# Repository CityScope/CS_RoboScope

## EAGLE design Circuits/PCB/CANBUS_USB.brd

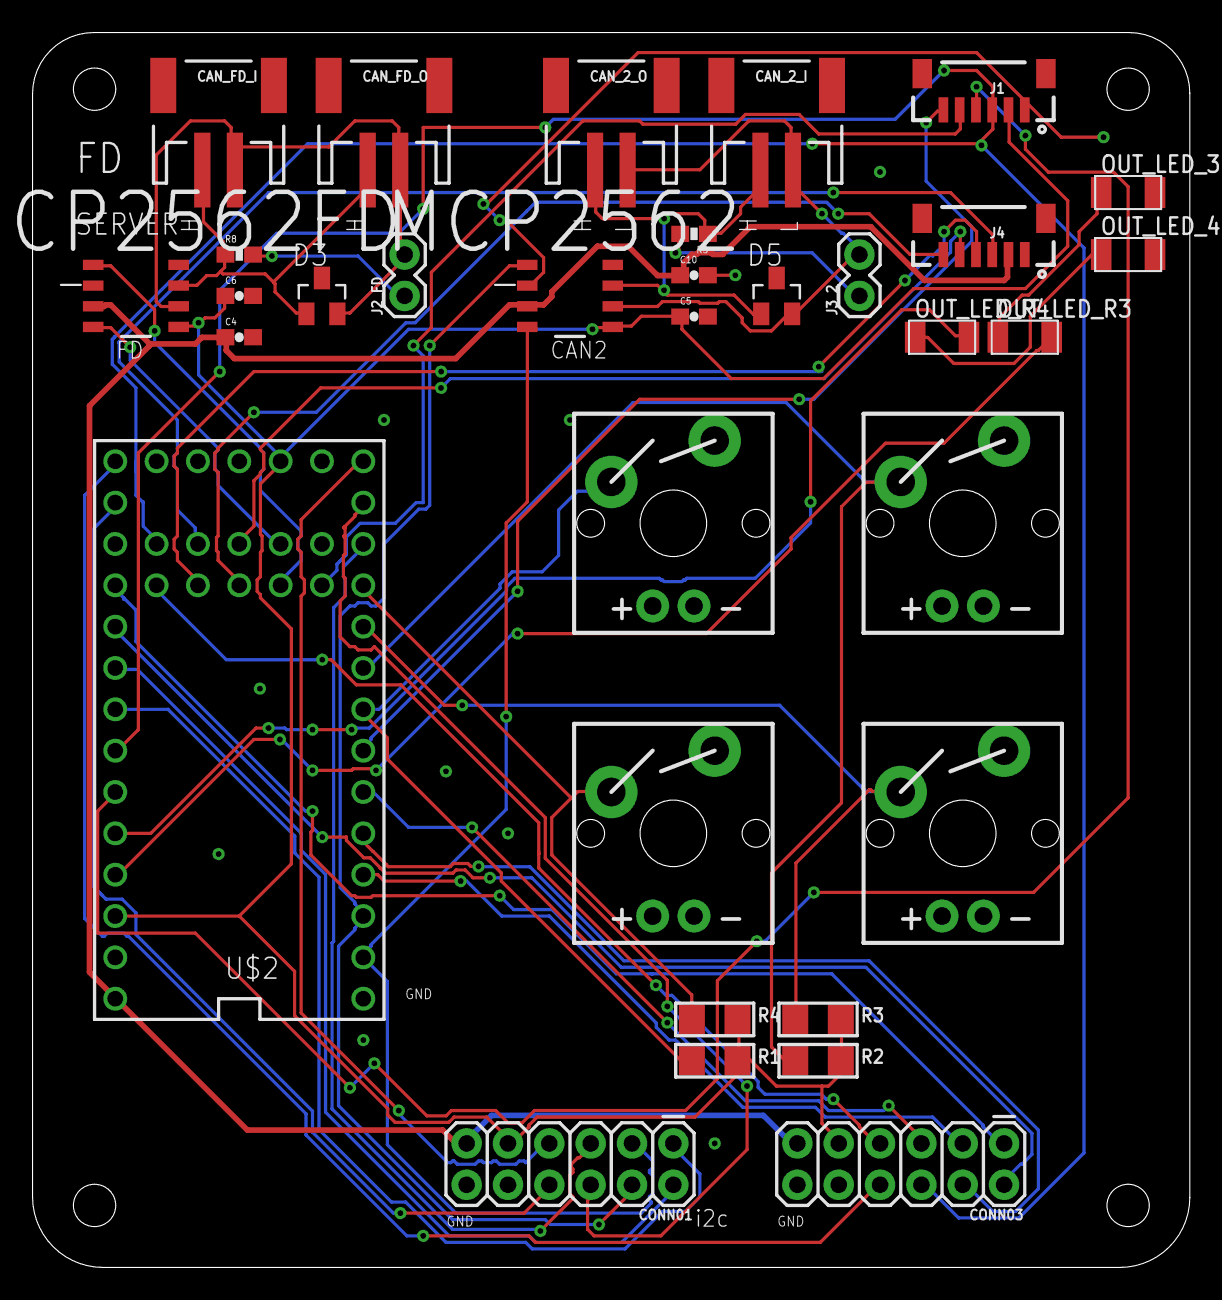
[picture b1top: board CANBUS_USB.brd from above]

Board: 2 copper layers, 71.1 x 75.9 mm, 33 parts (0 on the bottom side), 43 nets.

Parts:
C4, C5, C6, C10: 0.1uf; 0603-CAP
CAN_2_I, CAN_2_O: JST-2-SMD
CAN_FD_I: JST-2-SMD
CAN_FD_O: JST-2-SMD
CONN01, CONN03: 2X6 FEMALE; 2X6
D3, D5: PESD1CAN; SOT23
J1, J4: 1X06-1MM
J2_FD, J3_2: 1X02
MCP2562, MCP2562FD: MCP2562
OUT_LED_3, OUT_LED_4: LEDFAB1206; LED1206FAB
OUT_LED_R3, OUT_LED_R4: 500; R1206FAB
R1, R2, R3, R4: 1206
R5: 120Ohms; 0603-RES
R8: 120Ohms FD; 0603-RES
S1, S2, S3, S4: CHERRY-MX-LED
U$2: TEENSY_4.0_WITH_SMD_HEADER_PINS

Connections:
3.3V: C5.1, C6.1, CONN01.9, CONN03.9, J1.2, MCP2562.VIO, MCP2562FD.VIO, R1.2, R2.2, R3.2, R4.2, U$2.3.3V, U$2.3.3V1
CAN_H: CAN_FD_I.1, CAN_FD_O.1, D3.1, MCP2562FD.CANH, R8.1
CAN_H1: CAN_2_I.1, CAN_2_O.1, D5.1, MCP2562.CANH, R5.1
CAN_L: CAN_FD_I.2, CAN_FD_O.2, D3.2, J2_FD.2, MCP2562FD.CANL
CAN_L1: CAN_2_I.2, CAN_2_O.2, D5.2, J3_2.2, MCP2562.CANL
CAN_RX2: CONN01.3, MCP2562.RXD, U$2.0
CAN_RX3: MCP2562FD.RXD, U$2.30
CAN_TX2: CONN01.4, MCP2562.TXD, U$2.1
CAN_TX3: MCP2562FD.TXD, U$2.31
GND_MCU: C4.2, C5.2, C6.2, C10.2, CONN01.10, CONN01.12, CONN03.10, CONN03.12, D3.3, D5.3, J1.1, J4.1, MCP2562.STBY, MCP2562.VSS, MCP2562FD.STBY, MCP2562FD.VSS, OUT_LED_3.2, OUT_LED_4.2, S1.S2, S2.S2, S3.S2, S4.S2, U$2.GND, U$2.GND1, U$2.GND2
GPIO_01: CONN03.3, U$2.2
GPIO_02: CONN03.4, U$2.3
GPIO_03: CONN03.5, U$2.4
GPIO_04: CONN01.5, U$2.10
GPIO_05: CONN01.6, U$2.11
GPIO_06: CONN01.7, U$2.12
GPIO_07: CONN03.8, U$2.13
GPIO_08: CONN01.8, U$2.14/A0
GPIO_10: CONN03.1, U$2.16/A2
GPIO_11: CONN03.2, U$2.17/A3
GPIO_12: J1.3, U$2.20/A6
GPIO_13: J1.4, U$2.21/A7
GPIO_14: CONN03.7, U$2.25
GPIO_15: J4.3, U$2.26
GPIO_16: J4.4, U$2.27
GPIO_17: J4.5, U$2.28
GPIO_18: J4.6, U$2.29
GPIO_20: CONN03.6, U$2.24
GPIO_SCL: CONN01.1, U$2.19/A5
GPIO_SDA: CONN01.2, U$2.18/A4
KEY_01: R1.1, S1.S1, U$2.6
KEY_02: R2.1, S2.S1, U$2.7
KEY_03: R3.1, S3.S1, U$2.8
KEY_04: R4.1, S4.S1, U$2.9
LED_15: OUT_LED_R4.2, U$2.22/A8
LED_16: OUT_LED_R3.2, U$2.23/A9
unnamed: J2_FD.1, R8.2
unnamed: J3_2.1, R5.2
unnamed: OUT_LED_3.1, OUT_LED_R3.1
unnamed: OUT_LED_4.1, OUT_LED_R4.1
SWITCH_01: J1.6, U$2.5
SWITCH_02: J1.5, U$2.33
VCC_5V: C4.1, C10.1, CONN01.11, CONN03.11, J4.2, MCP2562.VDD, MCP2562FD.VDD, U$2.VIN

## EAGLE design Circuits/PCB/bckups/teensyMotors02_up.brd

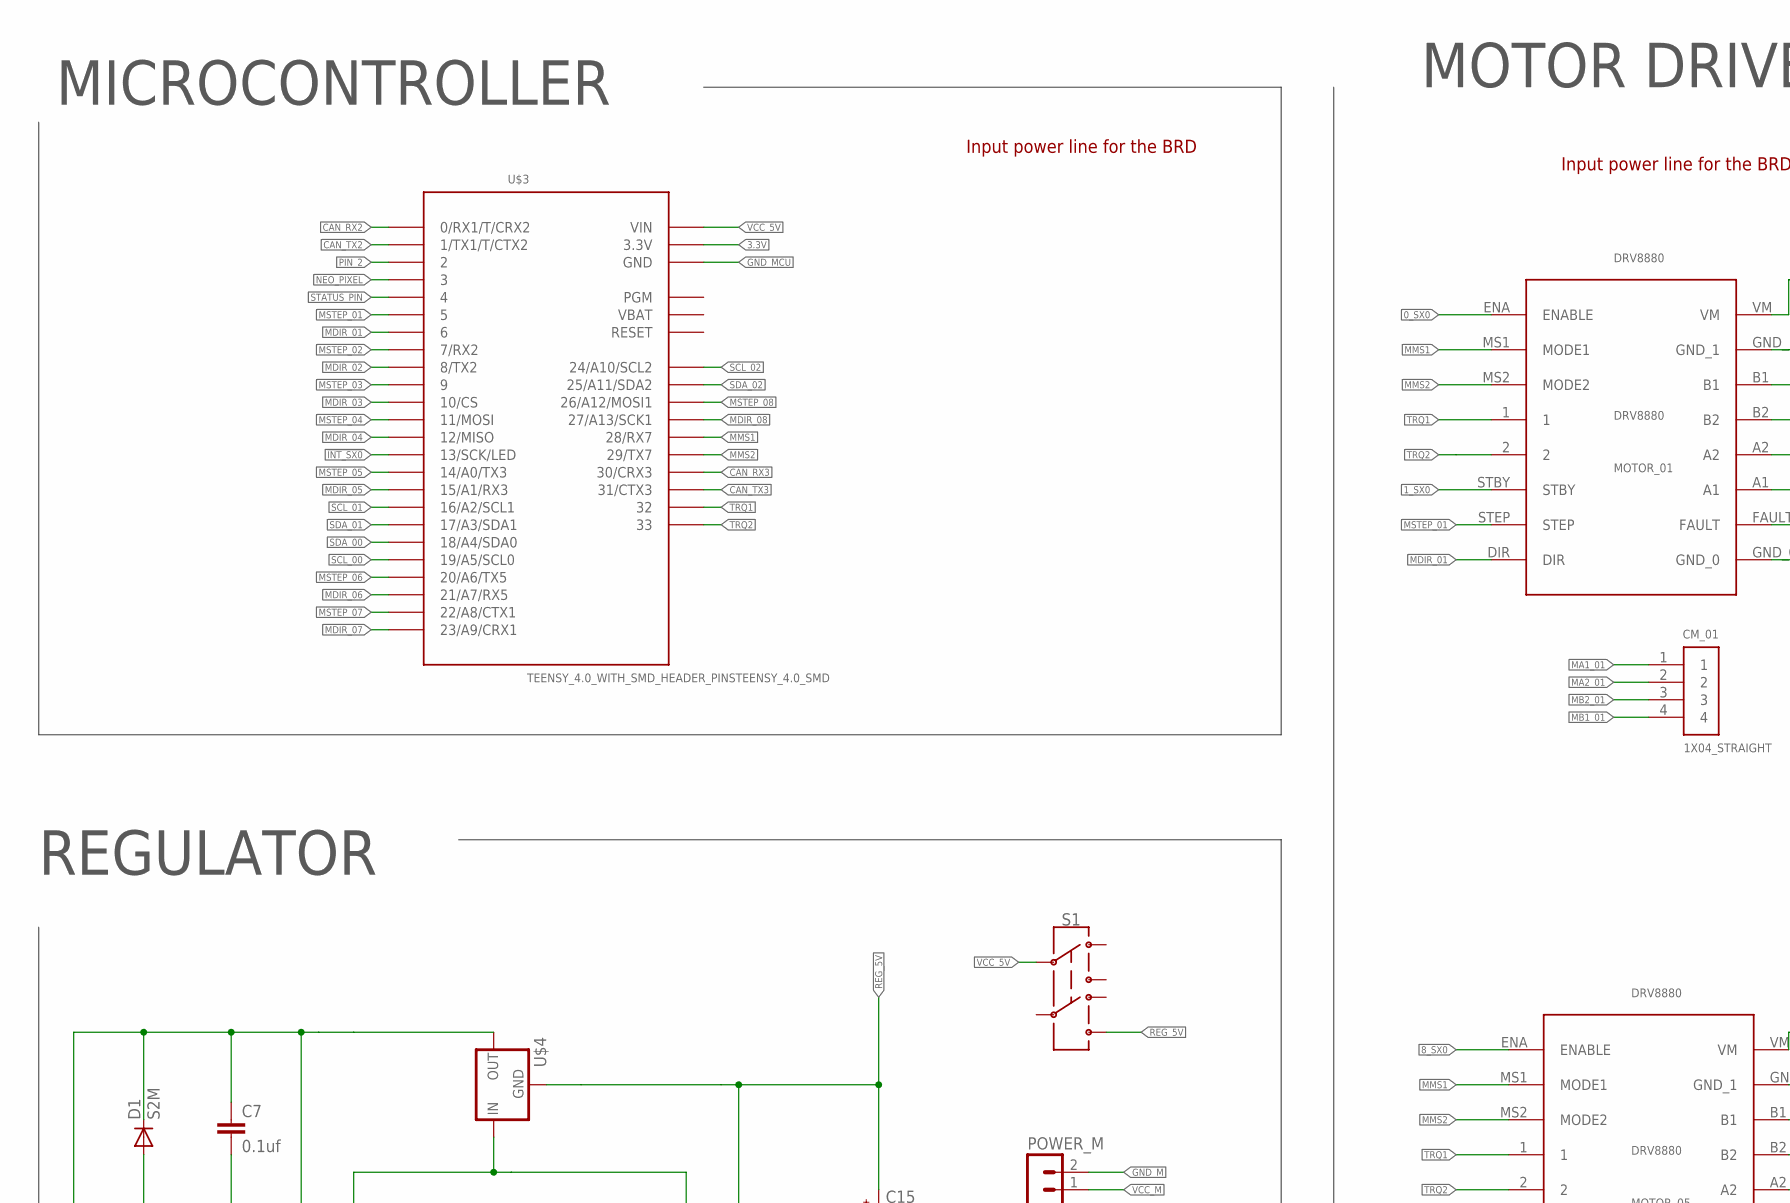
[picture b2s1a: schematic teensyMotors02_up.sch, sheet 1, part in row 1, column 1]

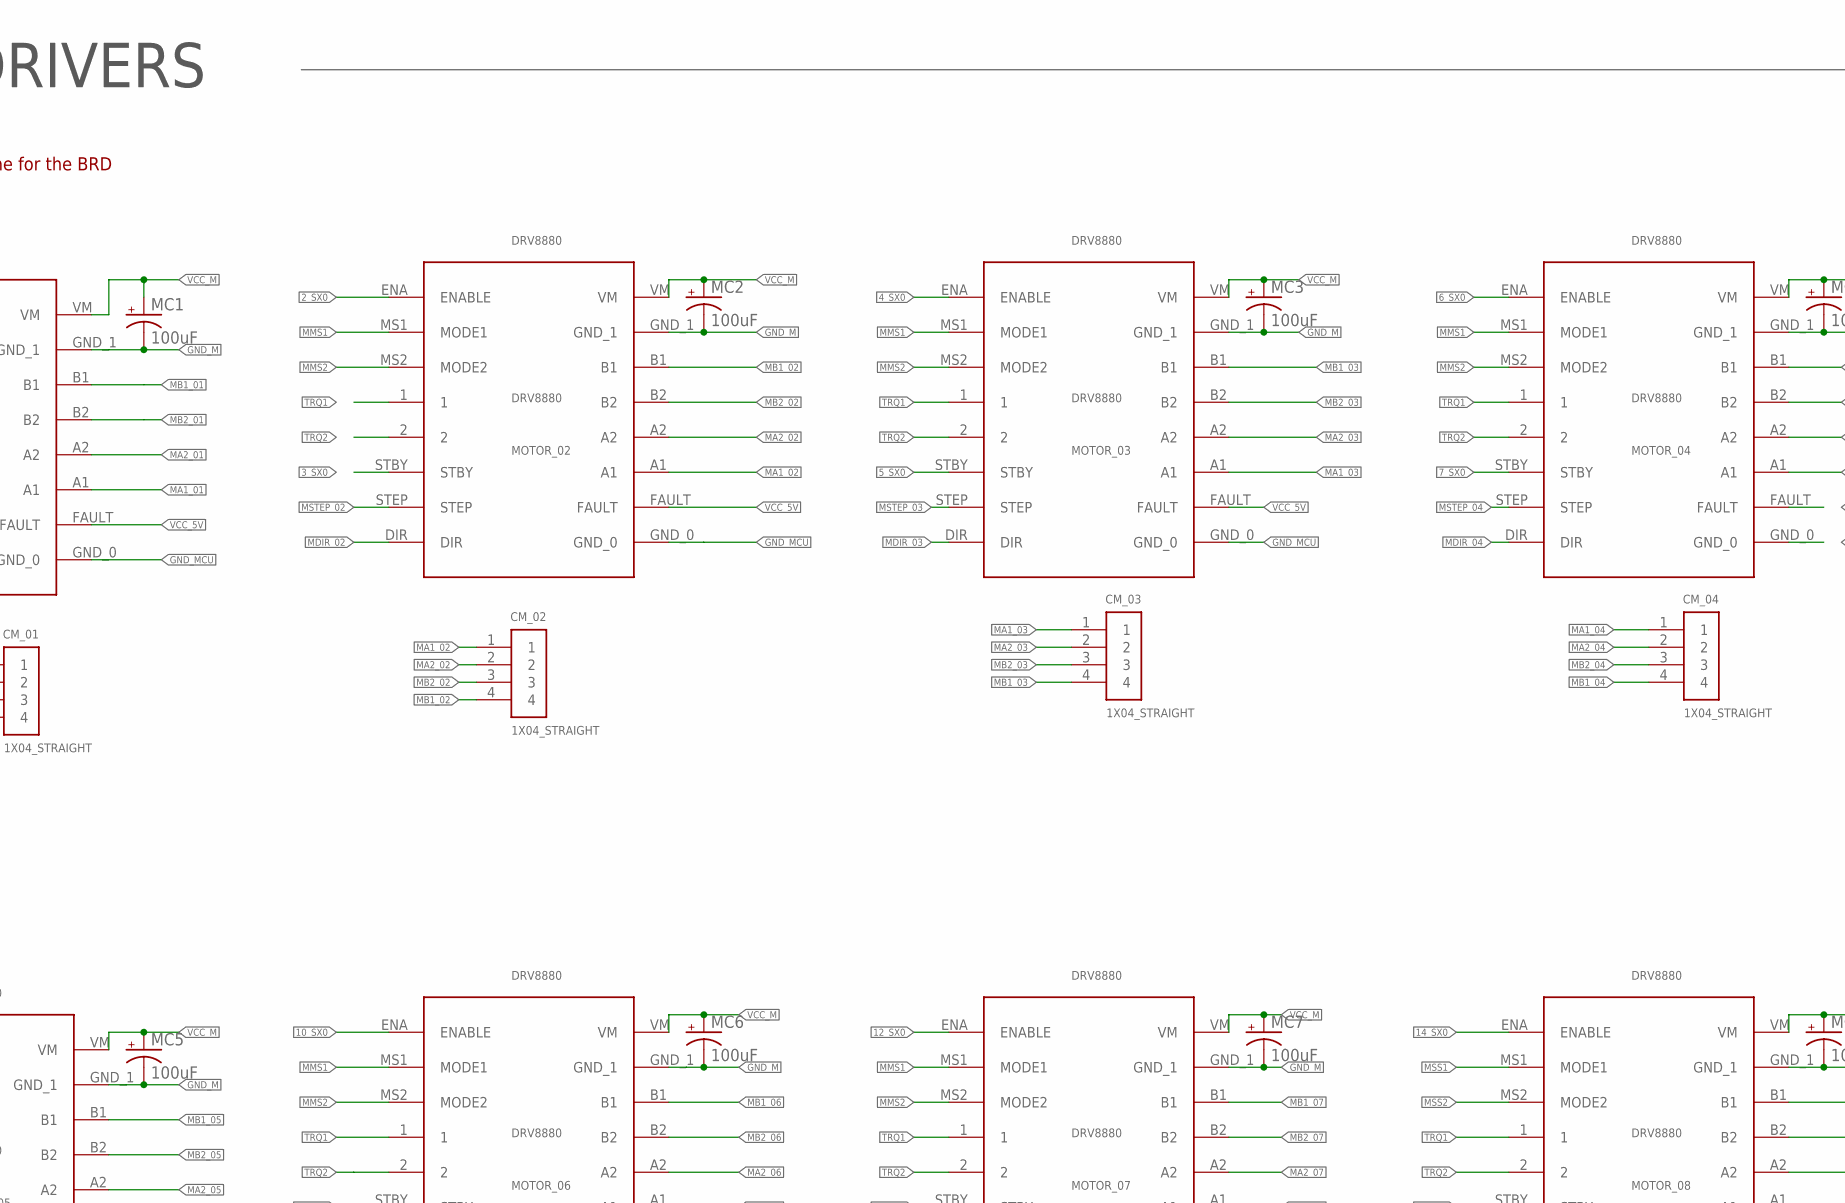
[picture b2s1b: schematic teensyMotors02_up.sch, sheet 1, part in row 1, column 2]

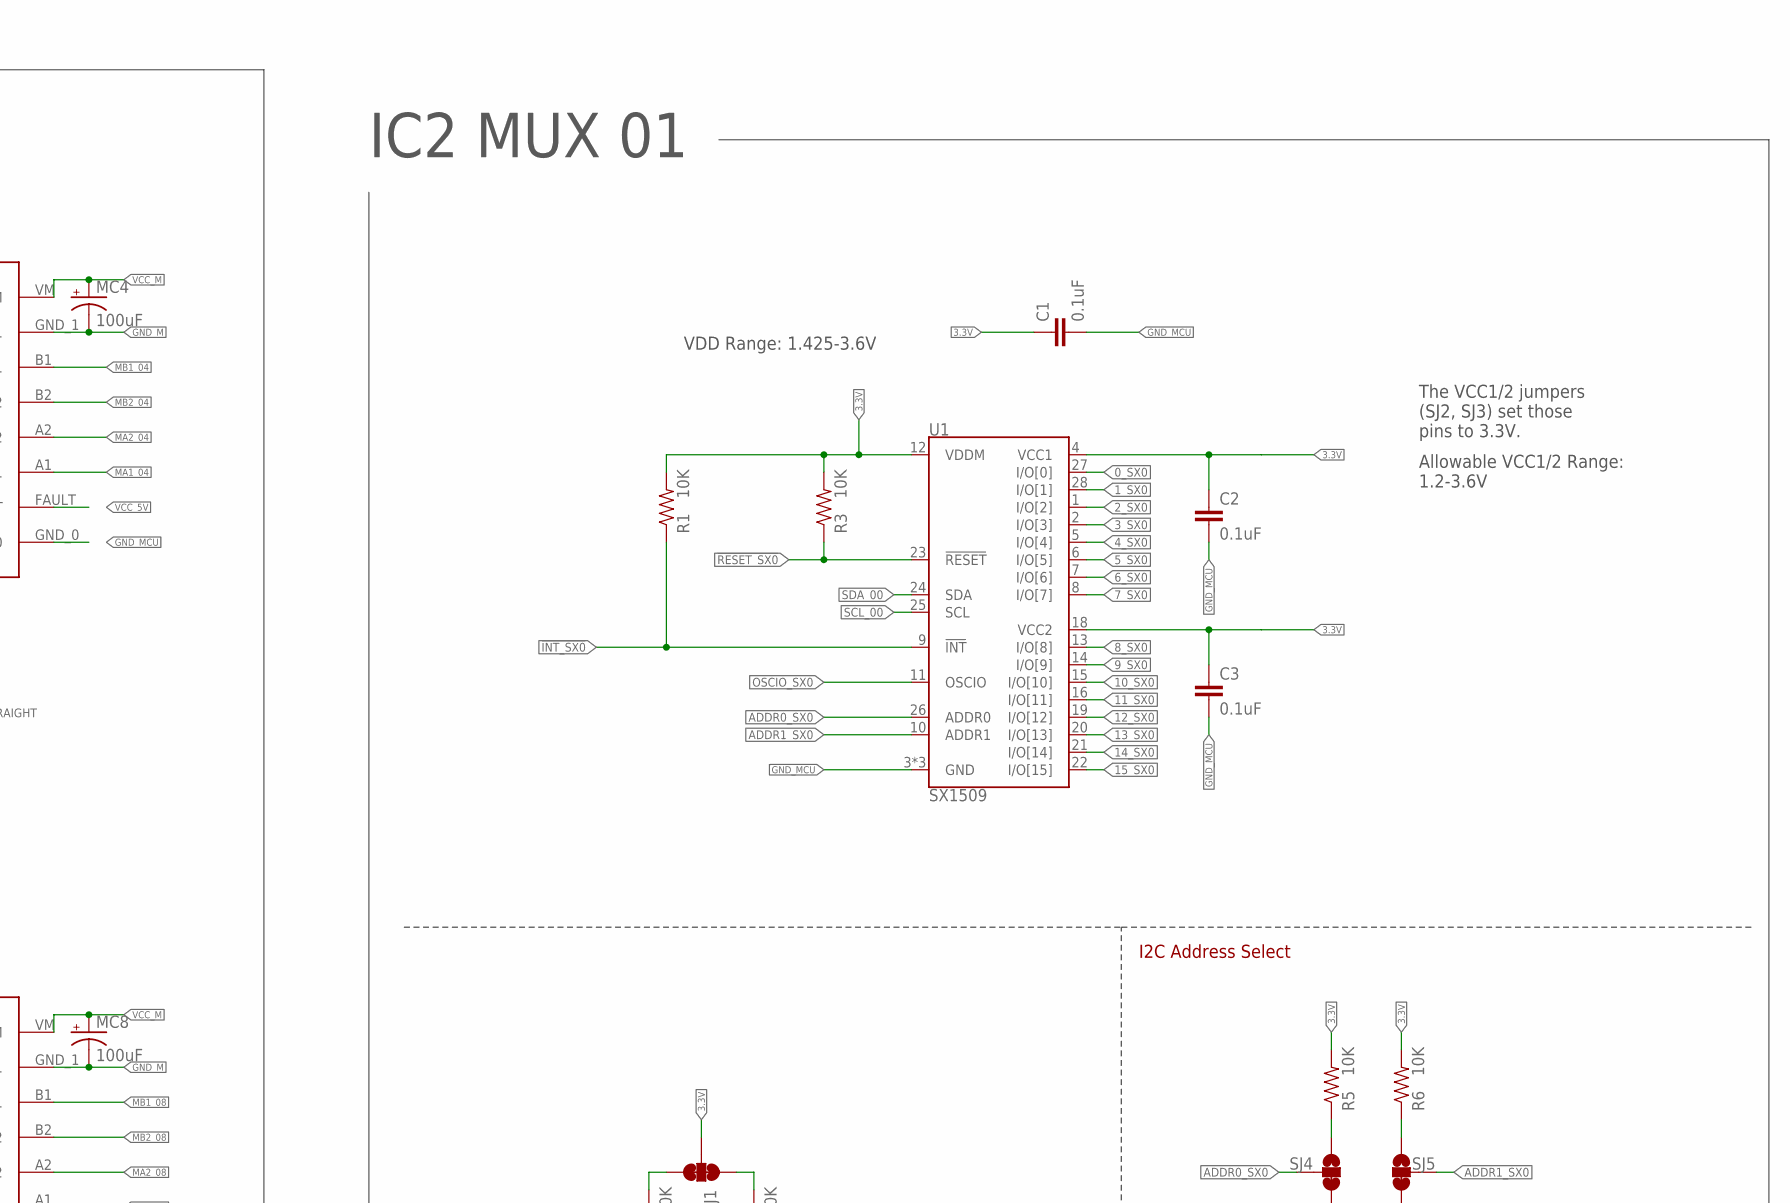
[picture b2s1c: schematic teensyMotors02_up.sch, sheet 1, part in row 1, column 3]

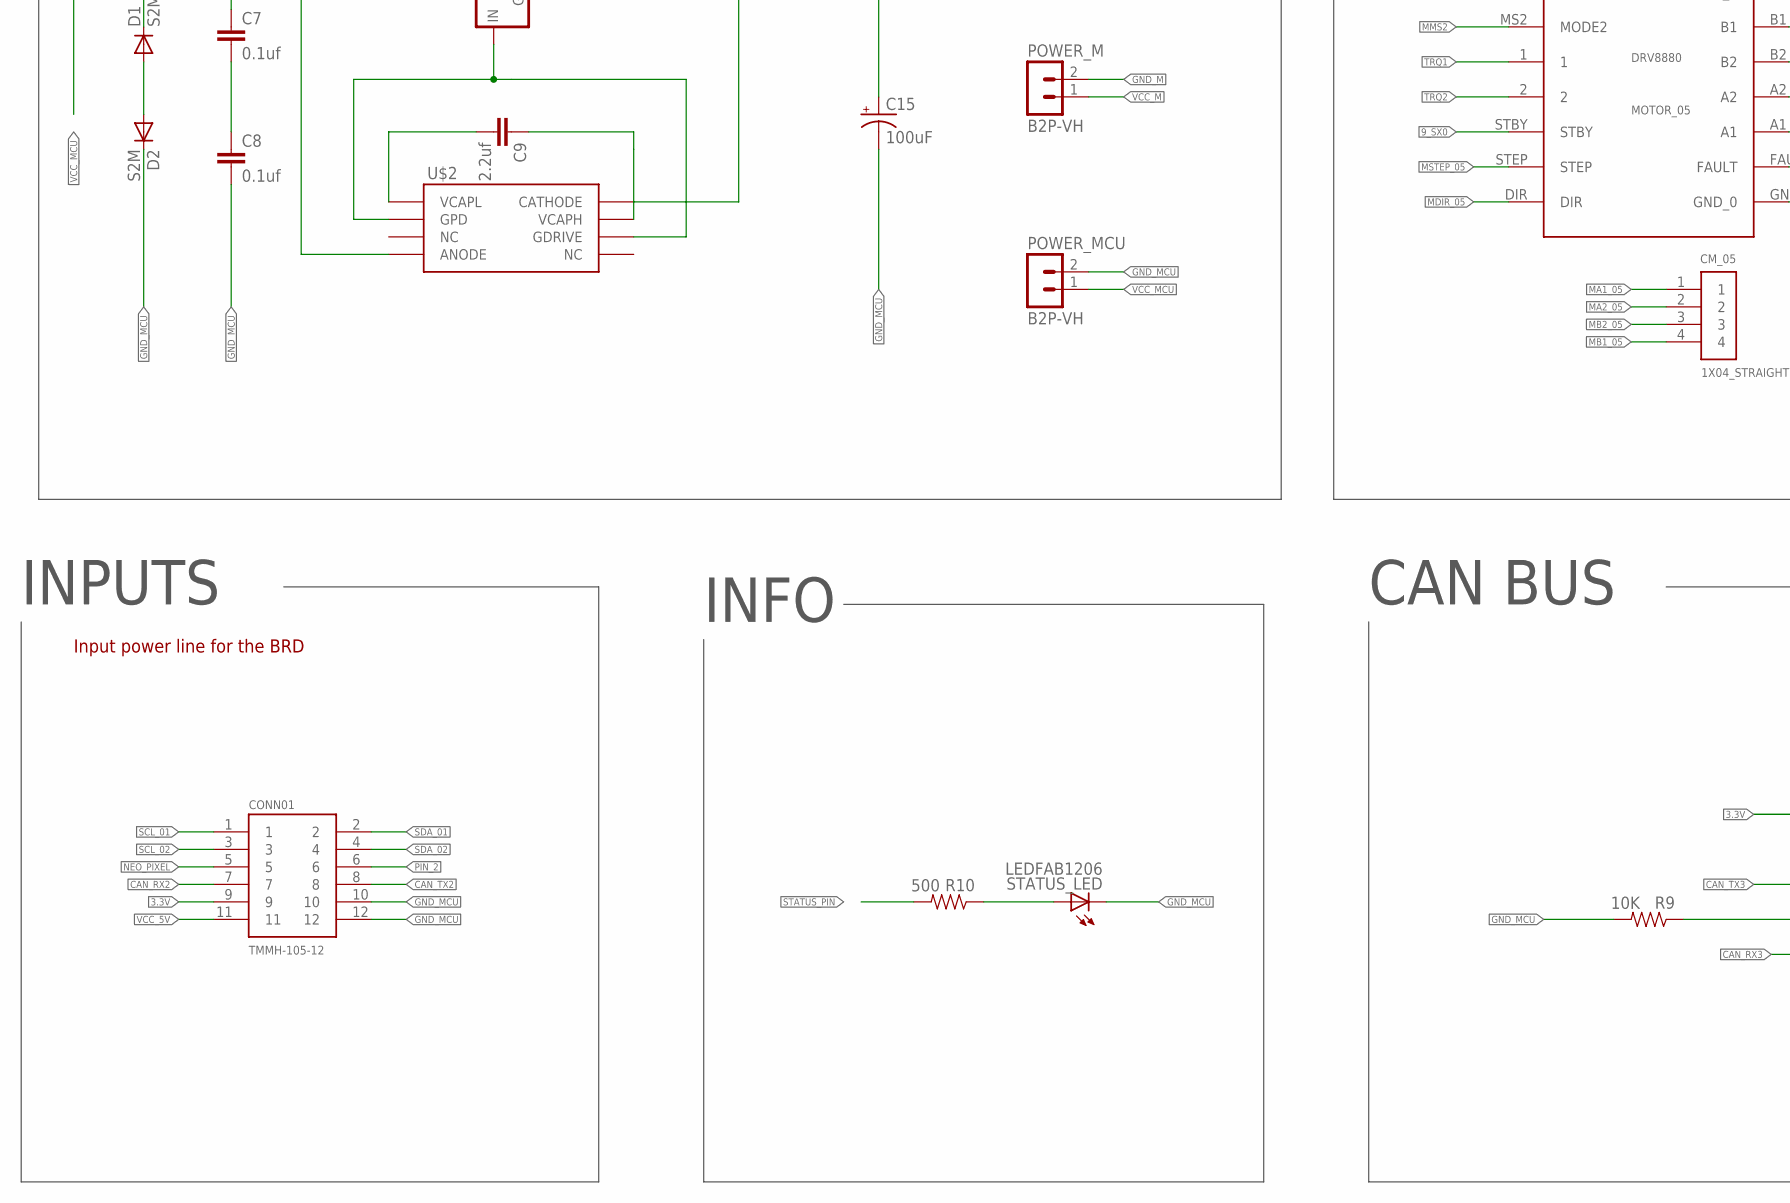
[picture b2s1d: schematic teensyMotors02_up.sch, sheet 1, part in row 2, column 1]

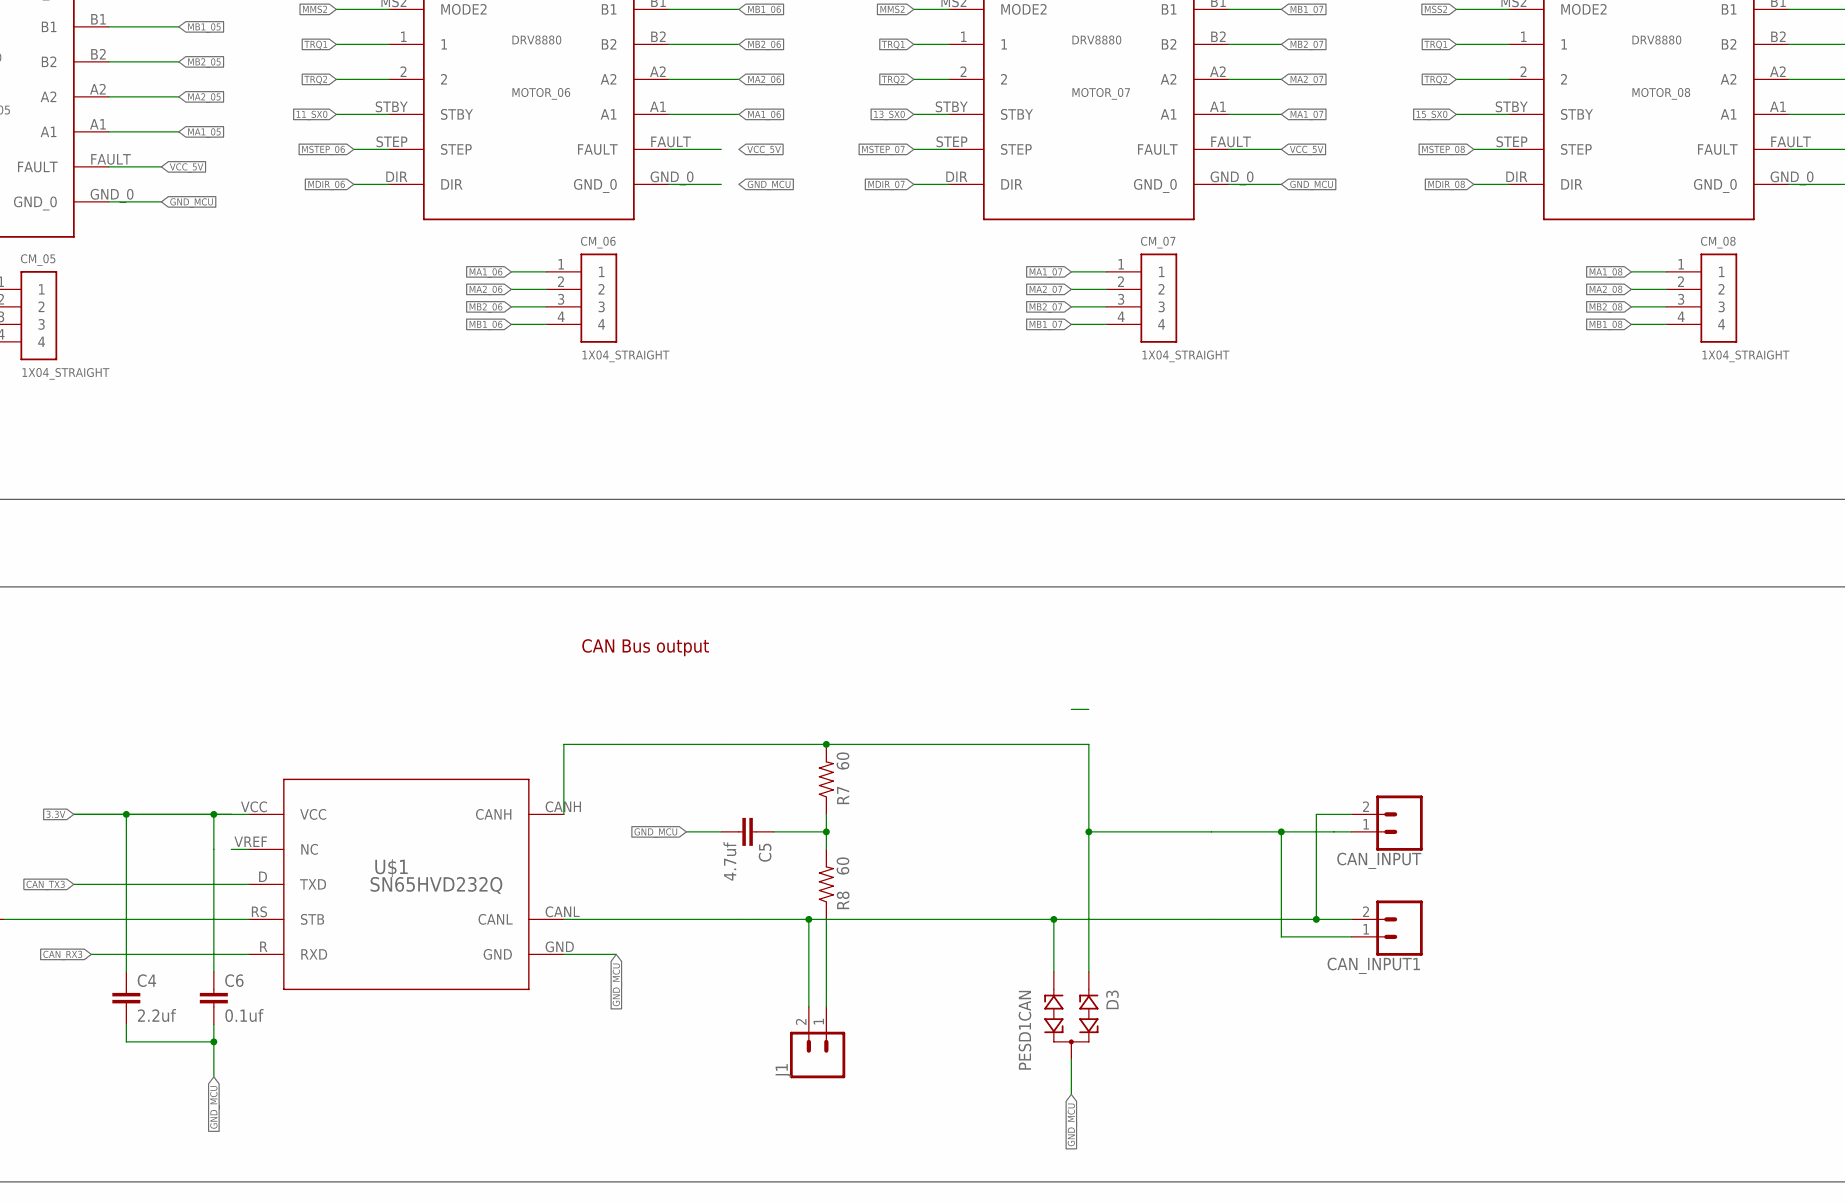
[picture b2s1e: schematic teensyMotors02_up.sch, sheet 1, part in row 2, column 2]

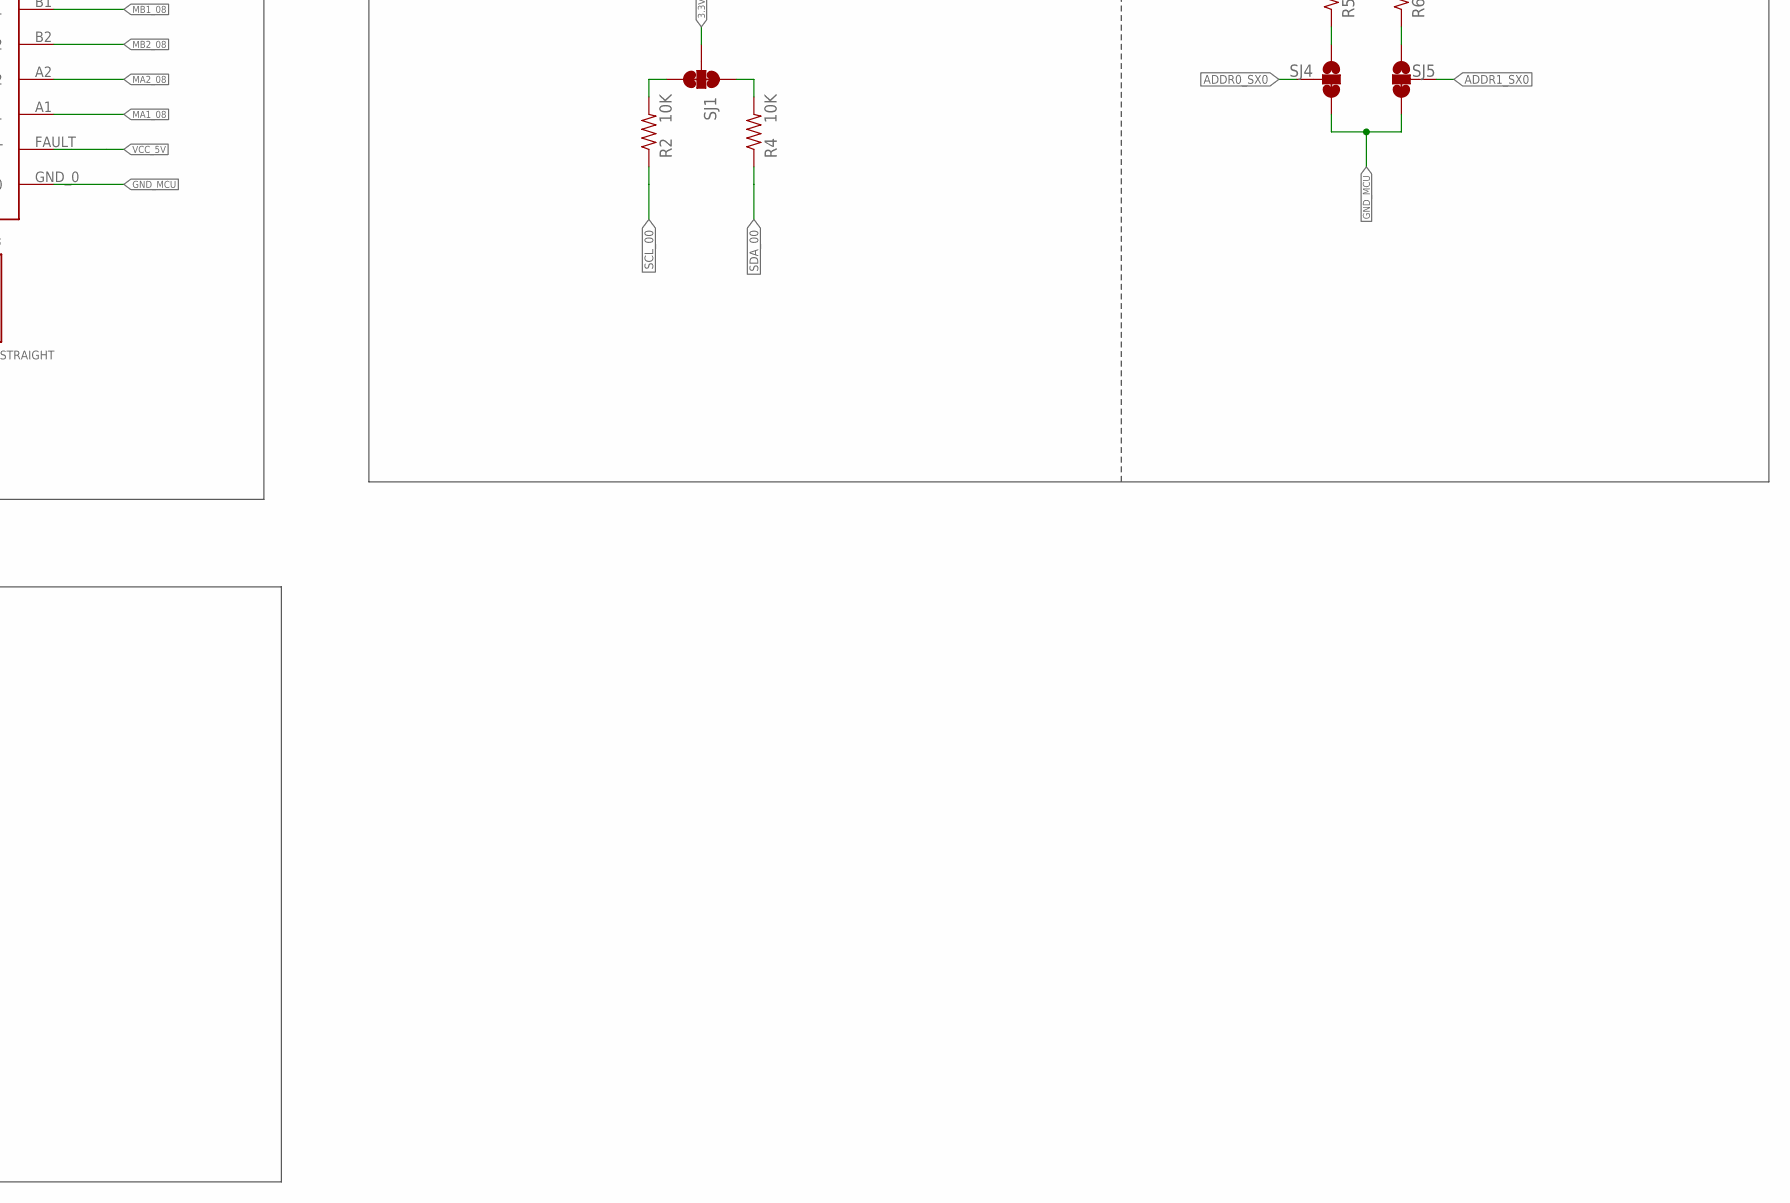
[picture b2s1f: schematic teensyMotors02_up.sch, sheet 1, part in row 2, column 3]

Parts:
C1, C2, C3: 0.1uF; 0603-CAP
C4, C9: 2.2uf; 0603-CAP
C5: 4.7uf; 0603-CAP
C6, C7, C8: 0.1uf; 0603-CAP
C15: 100uF; PANASONIC_D
CAN_INPUT, CAN_INPUT1: CONN_02-JST-2MM-SMT; JST-2-SMD
CM_01, CM_02, CM_03, CM_04, CM_05, CM_06, CM_07, CM_08: 1X04_STRAIGHT; 1X04-CLEANBIG
CONN01: TMMH-105-12
D1, D2: S2M; DO214AA
D3: PESD1CAN; SOT23
J1: CONN_02; 1X02
MC1, MC2, MC3, MC4, MC5, MC6, MC7, MC8: 100uF; PANASONIC_D
MOTOR_01, MOTOR_02, MOTOR_03, MOTOR_04, MOTOR_05, MOTOR_06, MOTOR_07, MOTOR_08: DRV8880
POWER_M: B2P-VH
POWER_MCU: B2P-VH
R1, R2, R3, R4, R5, R6, R9: 10K; 0603-RES
R7, R8: 60; 0603-RES
R10: 500; 0603-RES
S1: SWITCH-DPDT-SMD-AYZ0202; SWITCH_DPDT_SMD_AYZ0202
SJ1: JUMPER-PAD-3-NC_BY_TRACE; PAD-JUMPER-3-3OF3_NC_BY_TRACE_YES_SILK_FULL_BOX
SJ4, SJ5: JUMPER-PAD-3-2OF3_NC_BY_TRACE_SMALL; PAD-JUMPER-3-2OF3_NC_BY_TRACE_YES_SILK_FULL_BOX
STATUS_LED: LEDFAB1206; LED1206FAB
U1: SX1509; QFN-28
U$1: SN65HVD232Q
U$2: LM74610-Q1; VSSOP(8)
U$3: TEENSY_4.0_WITH_SMD_HEADER_PINSTEENSY_4.0_SMD; TEENSY_4.0_SMD
U$4: BUK; TO263-3

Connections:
0_SX0: MOTOR_01.ENA (ENABLE), U1.27 (I/O[0])
1_SX0: MOTOR_01.STBY, U1.28 (I/O[1])
2_SX0: MOTOR_02.ENA (ENABLE), U1.1 (I/O[2])
3.3V: C1.1, C2.1, C3.1, C4.1, C6.1, CONN01.9, R1.2, R3.2, R5.2, R6.2, SJ1.2, U1.4 (VCC1), U1.12 (VDDM), U1.18 (VCC2), U$1.VCC, U$3.3.3V, U$3.3.3V1 (3.3V)
3_SX0: MOTOR_02.STBY, U1.2 (I/O[3])
4_SX0: MOTOR_03.ENA (ENABLE), U1.5 (I/O[4])
5_SX0: MOTOR_03.STBY, U1.6 (I/O[5])
6_SX0: MOTOR_04.ENA (ENABLE), U1.7 (I/O[6])
7_SX0: MOTOR_04.STBY, U1.8 (I/O[7])
8_SX0: MOTOR_05.ENA (ENABLE), U1.13 (I/O[8])
9_SX0: MOTOR_05.STBY, U1.14 (I/O[9])
10_SX0: MOTOR_06.ENA (ENABLE), U1.15 (I/O[10])
11_SX0: MOTOR_06.STBY, U1.16 (I/O[11])
12_SX0: MOTOR_07.ENA (ENABLE), U1.19 (I/O[12])
13_SX0: MOTOR_07.STBY, U1.20 (I/O[13])
14_SX0: MOTOR_08.ENA (ENABLE), U1.21 (I/O[14])
15_SX0: MOTOR_08.STBY, U1.22 (I/O[15])
!INT_SX0: R1.1, U1.9 (!INT), U$3.13 (13/SCK/LED)
!RESET_SX0: R3.1, U1.23 (!RESET)
ADDR0_SX0: SJ4.2, U1.26 (ADDR0)
ADDR1_SX0: SJ5.2, U1.10 (ADDR1)
CAN_H: CAN_INPUT.1 (2), CAN_INPUT1.1 (2), D3.1, R7.2, U$1.CANH
CAN_L: CAN_INPUT.2 (1), CAN_INPUT1.2 (1), D3.2, J1.2, U$1.CANL
CAN_RX2: CONN01.7, U$3.0 (0/RX1/T/CRX2)
CAN_RX3: U$1.R (RXD), U$3.30 (30/CRX3)
CAN_TX2: CONN01.8, U$3.1 (1/TX1/T/CTX2)
CAN_TX3: U$1.D (TXD), U$3.31 (31/CTX3)
GND_M: MC1.-, MC2.-, MC3.-, MC4.-, MC5.-, MC6.-, MC7.-, MC8.-, MOTOR_01.GND_1, MOTOR_02.GND_1, MOTOR_03.GND_1, MOTOR_04.GND_1, MOTOR_05.GND_1, MOTOR_06.GND_1, MOTOR_07.GND_1, MOTOR_08.GND_1, POWER_M.2
GND_MCU: C1.2, C2.2, C3.2, C4.2, C5.2, C6.2, C8.2, C15.-, CONN01.10, CONN01.12, D2.C, D3.3, MOTOR_01.GND_0, MOTOR_02.GND_0, MOTOR_03.GND_0, MOTOR_04.GND_0, MOTOR_05.GND_0, MOTOR_06.GND_0, MOTOR_07.GND_0, MOTOR_08.GND_0, POWER_MCU.2, R9.2, SJ4.3, SJ5.3, STATUS_LED.2 (C), U1.3 (GND), U1.17 (GND), U1.29 (GND), U$1.GND, U$3.GND, U$3.GND1 (GND), U$3.GND2 (GND)
MA1_01: CM_01.1, MOTOR_01.A1
MA1_02: CM_02.1, MOTOR_02.A1
MA1_03: CM_03.1, MOTOR_03.A1
MA1_04: CM_04.1, MOTOR_04.A1
MA1_05: CM_05.1, MOTOR_05.A1
MA1_06: CM_06.1, MOTOR_06.A1
MA1_07: CM_07.1, MOTOR_07.A1
MA1_08: CM_08.1, MOTOR_08.A1
MA2_01: CM_01.2, MOTOR_01.A2
MA2_02: CM_02.2, MOTOR_02.A2
MA2_03: CM_03.2, MOTOR_03.A2
MA2_04: CM_04.2, MOTOR_04.A2
MA2_05: CM_05.2, MOTOR_05.A2
MA2_06: CM_06.2, MOTOR_06.A2
MA2_07: CM_07.2, MOTOR_07.A2
MA2_08: CM_08.2, MOTOR_08.A2
MB1_01: CM_01.4, MOTOR_01.B1
MB1_02: CM_02.4, MOTOR_02.B1
MB1_03: CM_03.4, MOTOR_03.B1
MB1_04: CM_04.4, MOTOR_04.B1
MB1_05: CM_05.4, MOTOR_05.B1
MB1_06: CM_06.4, MOTOR_06.B1
MB1_07: CM_07.4, MOTOR_07.B1
MB1_08: CM_08.4, MOTOR_08.B1
MB2_01: CM_01.3, MOTOR_01.B2
MB2_02: CM_02.3, MOTOR_02.B2
MB2_03: CM_03.3, MOTOR_03.B2
MB2_04: CM_04.3, MOTOR_04.B2
MB2_05: CM_05.3, MOTOR_05.B2
MB2_06: CM_06.3, MOTOR_06.B2
MB2_07: CM_07.3, MOTOR_07.B2
MB2_08: CM_08.3, MOTOR_08.B2
MDIR_01: MOTOR_01.DIR, U$3.6
MDIR_02: MOTOR_02.DIR, U$3.8 (8/TX2)
MDIR_03: MOTOR_03.DIR, U$3.10 (10/CS)
MDIR_04: MOTOR_04.DIR, U$3.12 (12/MISO)
MDIR_05: MOTOR_05.DIR, U$3.15/A1 (15/A1/RX3)
MDIR_06: MOTOR_06.DIR, U$3.21/A7 (21/A7/RX5)
MDIR_07: MOTOR_07.DIR, U$3.23/A9 (23/A9/CRX1)
MDIR_08: MOTOR_08.DIR, U$3.27 (27/A13/SCK1)
MMS1: MOTOR_01.MS1 (MODE1), MOTOR_02.MS1 (MODE1), MOTOR_03.MS1 (MODE1), MOTOR_04.MS1 (MODE1), MOTOR_05.MS1 (MODE1), MOTOR_06.MS1 (MODE1), MOTOR_07.MS1 (MODE1), U$3.28 (28/RX7)
MMS2: MOTOR_01.MS2 (MODE2), MOTOR_02.MS2 (MODE2), MOTOR_03.MS2 (MODE2), MOTOR_04.MS2 (MODE2), MOTOR_05.MS2 (MODE2), MOTOR_06.MS2 (MODE2), MOTOR_07.MS2 (MODE2), U$3.29 (29/TX7)
MSS1: MOTOR_08.MS1 (MODE1)
MSS2: MOTOR_08.MS2 (MODE2)
MSTEP_01: MOTOR_01.STEP, U$3.5
MSTEP_02: MOTOR_02.STEP, U$3.7 (7/RX2)
MSTEP_03: MOTOR_03.STEP, U$3.9
MSTEP_04: MOTOR_04.STEP, U$3.11 (11/MOSI)
MSTEP_05: MOTOR_05.STEP, U$3.14/A0 (14/A0/TX3)
MSTEP_06: MOTOR_06.STEP, U$3.20/A6 (20/A6/TX5)
MSTEP_07: MOTOR_07.STEP, U$3.22/A8 (22/A8/CTX1)
MSTEP_08: MOTOR_08.STEP, U$3.26 (26/A12/MOSI1)
unnamed: R2.2, SJ1.3
unnamed: C9.1, U$2.VCAPH
unnamed: U$2.GDRIVE, U$2.GPD, U$4.1 (IN)
unnamed: C9.2, U$2.VCAPL
unnamed: R9.1, U$1.RS (STB)
unnamed: R4.2, SJ1.1
unnamed: R5.1, SJ4.1
unnamed: C7.2, C8.1
unnamed: R6.1, SJ5.1
unnamed: D1.A, D2.A
unnamed: C5.1, R7.1, R8.2
unnamed: J1.1, R8.1
unnamed: R10.1, STATUS_LED.1 (A)
NEO_PIXEL: CONN01.5, U$3.3
OSCIO_SX0: U1.11 (OSCIO)
PIN_2: CONN01.6, U$3.2
REG_5V: C15.+, S1.6, U$2.CATHODE, U$4.4 (GND)
SCL_00: R2.1, U1.25 (SCL), U$3.19/A5 (19/A5/SCL0)
SCL_01: CONN01.1, U$3.16/A2 (16/A2/SCL1)
SCL_02: CONN01.3, U$3.24 (24/A10/SCL2)
SDA_00: R4.1, U1.24 (SDA), U$3.18/A4 (18/A4/SDA0)
SDA_01: CONN01.2, U$3.17/A3 (17/A3/SDA1)
SDA_02: CONN01.4, U$3.25 (25/A11/SDA2)
STATUS_PIN: R10.2, U$3.4
TRQ1: MOTOR_01.1, MOTOR_02.1, MOTOR_03.1, MOTOR_04.1, MOTOR_05.1, MOTOR_06.1, MOTOR_07.1, MOTOR_08.1, U$3.32
TRQ2: MOTOR_01.2, MOTOR_02.2, MOTOR_03.2, MOTOR_04.2, MOTOR_05.2, MOTOR_06.2, MOTOR_07.2, MOTOR_08.2, U$3.33
VBAT: U$3.VBAT
VCC_5V: CONN01.11, MOTOR_01.FAULT, MOTOR_02.FAULT, MOTOR_03.FAULT, MOTOR_04.FAULT, MOTOR_05.FAULT, MOTOR_06.FAULT, MOTOR_07.FAULT, MOTOR_08.FAULT, S1.2, U$3.VIN
VCC_M: MC1.+, MC2.+, MC3.+, MC4.+, MC5.+, MC6.+, MC7.+, MC8.+, MOTOR_01.VM, MOTOR_02.VM, MOTOR_03.VM, MOTOR_04.VM, MOTOR_05.VM, MOTOR_06.VM, MOTOR_07.VM, MOTOR_08.VM, POWER_M.1
VCC_MCU: C7.1, D1.C, POWER_MCU.1, U$2.ANODE, U$4.3 (OUT)

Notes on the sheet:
MICROCONTROLLER
INPUTS
MOTOR DRIVERS
CAN BUS
CAN Bus output
Input power line for the BRD
INFO
REGULATOR
The VCC1/2 jumpers (SJ2, SJ3) set those pins to 3.3V.
I2C Address Select
VDD Range: 1.425-3.6V
Allowable VCC1/2 Range: 1.2-3.6V
IC2 MUX 01

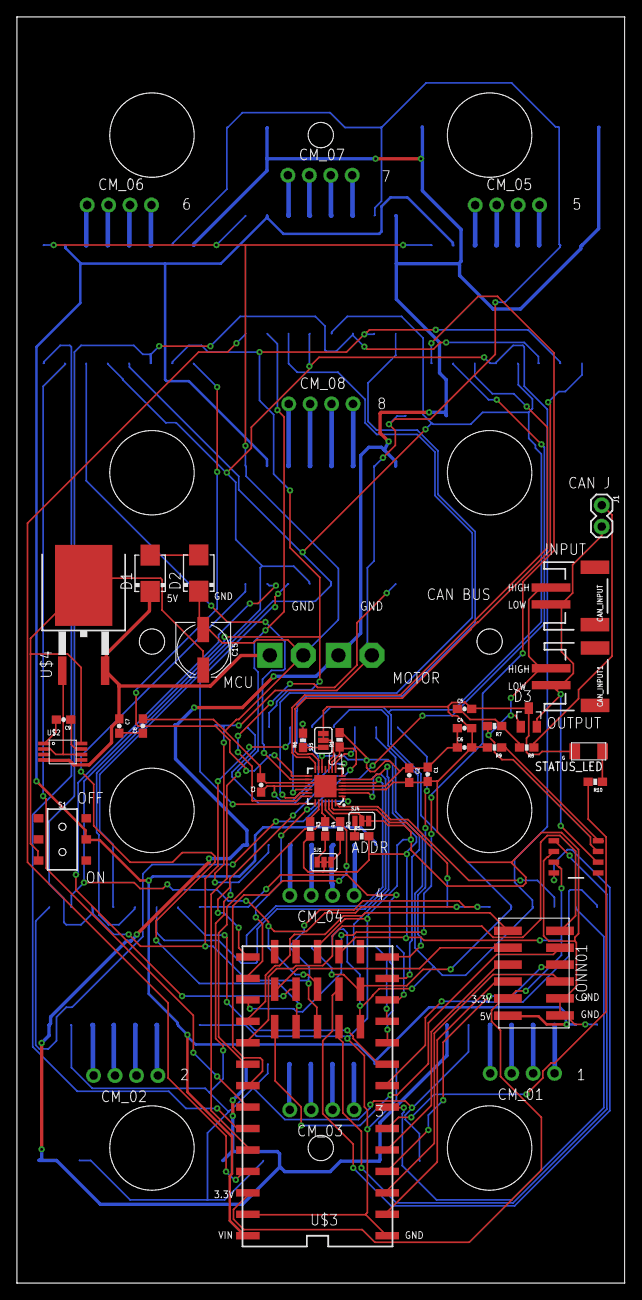
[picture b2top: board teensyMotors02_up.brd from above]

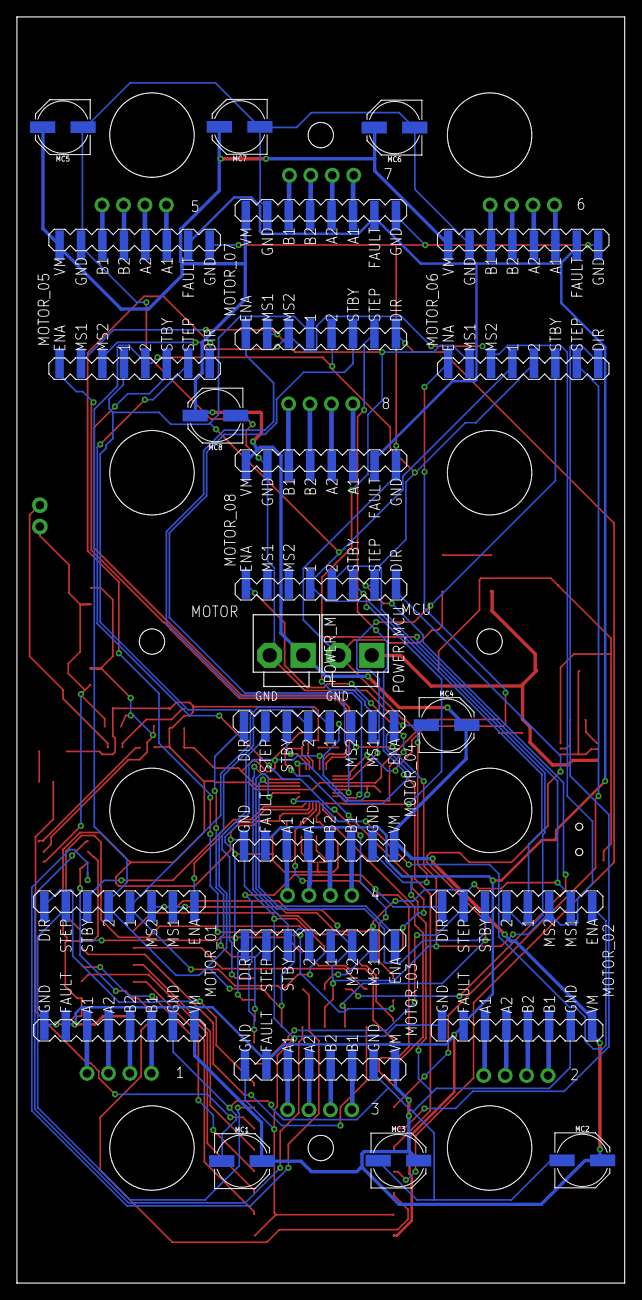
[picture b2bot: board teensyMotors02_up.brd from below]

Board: 4 copper layers, 72.0 x 150.0 mm, 63 parts (18 on the bottom side), 107 nets.

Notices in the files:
parts and their libraries:
SparkFun-Connectors: Licensing: Creative Commons ShareAlike 4.0 International - https://creativecommons.org/licenses/by-sa/4.0
microbuilder: This work is placed in the public domain, and may be freely used for commercial and non-commercial work with the following conditions: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
